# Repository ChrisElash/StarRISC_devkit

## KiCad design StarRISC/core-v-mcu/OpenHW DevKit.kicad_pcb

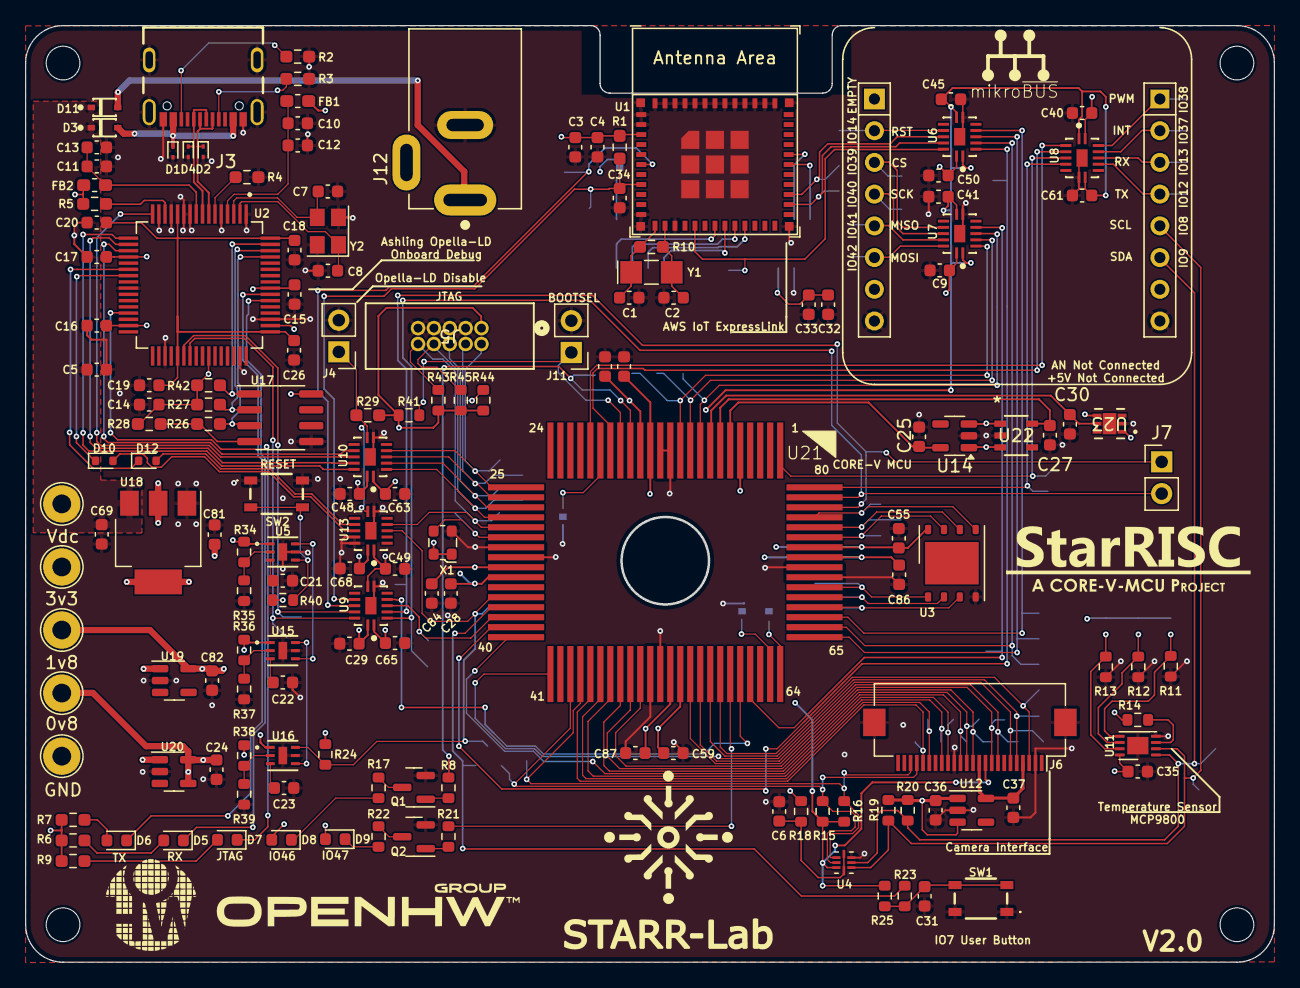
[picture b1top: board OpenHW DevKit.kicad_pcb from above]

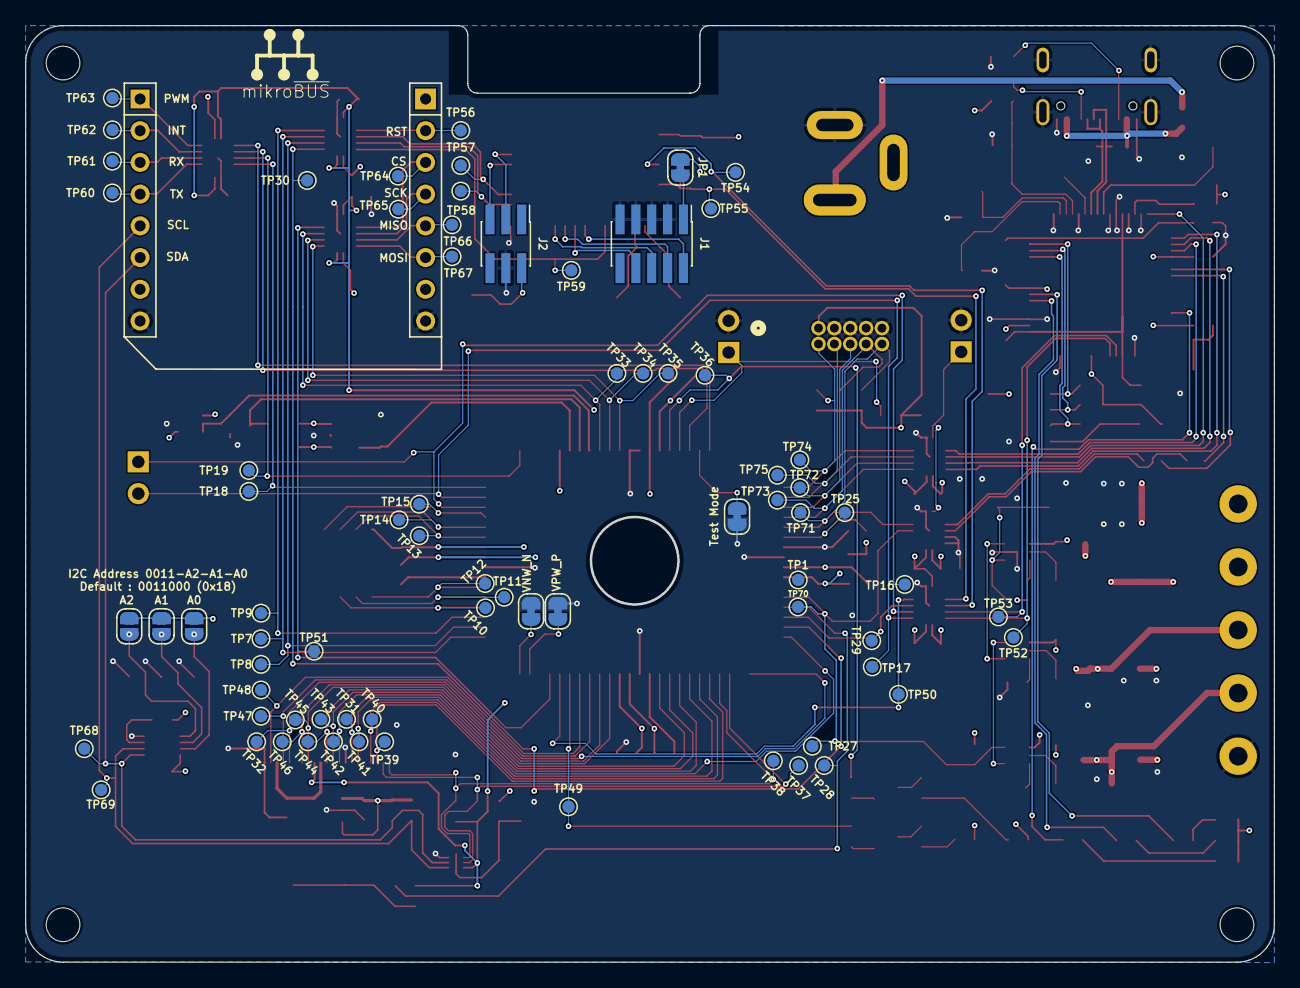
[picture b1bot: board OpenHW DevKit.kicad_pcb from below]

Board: 4 copper layers, 100.0 x 75.0 mm, 232 parts (73 on the bottom side), 139 nets.

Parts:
C1, C2, C7, C8: 12.5pF; C_0603_1608Metric
C3, C5, C30, C33, C69: 10uF; C_0603_1608Metric
C4, C6, C9, C12, C13, C14, C15, C16, C17, C18, C19, C20, C28, C29, C31, C34, C40, C41, C45, C48, C49, C50, C55, C57, C59, C61, C63, C65, C68, C84, C85, C86, C87: 100nF; C_0603_1608Metric
C10, C11: 4.7uF; C_0603_1608Metric
C21, C22, C23: 150pF; C_0603_1608Metric
C24, C25, C27, C36, C37, C82: 1uF; C_0603_1608Metric
C26: 3.3uF; C_0603_1608Metric
C32, C35: 100n; C_0603_1608Metric
C81: 22uF; C_0603_1608Metric
CON1: MIKROBUS_HOST_CONN
D1, D2, D4: ESD9B5.0ST5G; D_SOD-923
D3, D11: BAT760-7; Diodes-SOD323-03_2017-0-0
D5, D6, D7: LED_Small; LED_0603_1608Metric
D8, D9: LED; LED_0603_1608Metric
D10, D12: 1N914WT; D_SOD-523
FB1, FB2: Ferrite_Bead_Small; L_0603_1608Metric_Pad1.05x0.95mm_HandSolder
H1, H2, H3, H4: MountingHole; MountingHole_2.7mm_M2.5
J1: Conn_02x05_Odd_Even; PinHeader_2x05_P1.27mm_Vertical_SMD
J2: Conn_02x03_Odd_Even; PinHeader_2x03_P1.27mm_Vertical_SMD
J3: USB4105-GF-A; GCT_USB4105-GF-A
J4, J11: Conn_01x02_Male; PinHeader_1x02_P2.54mm_Vertical
J5: 3220-10-0100-00; CONN_3220-10-0100-00_CNC
J6: Conn_01x24; Hirose_FH12-24S-0.5SH_1x24-1MP_P0.50mm_Horizontal
J7: Conn_01x02_Pin; PinHeader_1x02_P2.54mm_Vertical
J12: PJ-002B; CUI_PJ-002B
JP1, JP2, JP6, JP9: SolderJumper_2_Bridged; SolderJumper-2_P1.3mm_Bridged_RoundedPad1.0x1.5mm
JP3, JP4, JP5: SolderJumper_2_Open; SolderJumper-2_P1.3mm_Open_RoundedPad1.0x1.5mm
Q1, Q2: MMBT3904; SOT-23
R1, R27, R28, R29, R42: 10k; R_0603_1608Metric_Pad0.98x0.95mm_HandSolder
R2, R3, R5: 5.1k; R_0603_1608Metric_Pad0.98x0.95mm_HandSolder
R4: 12k; R_0603_1608Metric_Pad0.98x0.95mm_HandSolder
R6, R7, R9, R26: 2.2k; R_0603_1608Metric_Pad0.98x0.95mm_HandSolder
R8, R21: 1k; R_0603_1608Metric
R10: 1M; R_0603_1608Metric_Pad0.98x0.95mm_HandSolder
R11, R12, R13, R14: 47k; R_0603_1608Metric
R15, R16, R19, R20, R25, R40: 4.7k; R_0603_1608Metric
R17, R22: 220; R_0603_1608Metric
R18: 200k; R_0603_1608Metric
R23: 100; R_0603_1608Metric
R24: 100k; R_0603_1608Metric
R34: 65k; R_0603_1608Metric
R35, R37, R39, R41, R43, R44, R45: 10k; R_0603_1608Metric
R36: 32.5k; R_0603_1608Metric
R38: 7.5k; R_0603_1608Metric
SW1, SW2: SW_Push; TS204225WT160SMTTR
TP1: TestPoint; TestPoint_Pad_D1.0mm
TP2: Vdc; TestPoint_Loop_D2.54mm_Drill1.5mm_Beaded
TP3: 3v3; TestPoint_Loop_D2.54mm_Drill1.5mm_Beaded
TP4: 1v8; TestPoint_Loop_D2.54mm_Drill1.5mm_Beaded
TP5: 0v8; TestPoint_Loop_D2.54mm_Drill1.5mm_Beaded
TP6: GND; TestPoint_Loop_D2.54mm_Drill1.5mm_Beaded
TP7, TP8, TP9, TP10, TP11, TP12, TP13, TP14, TP15, TP16, TP17, TP18, TP19, TP25, TP27, TP28, TP29, TP30, TP31, TP32, TP33, TP34, TP35, TP36, TP37, TP38, TP39, TP40, TP41, TP42, TP43, TP44, TP45, TP46, TP47, TP48, TP49, TP50, TP51, TP52, TP53, TP54, TP55, TP56, TP57, TP58, TP59, TP60, TP61, TP62, TP63, TP64, TP65, TP66, TP67, TP68, TP69, TP70, TP71, TP72, TP73, TP74, TP75: TestPoint_Small; TestPoint_Pad_D1.0mm
U1: ESP32-C3-MINI-1
U2: FT2232HL-REEL; QFP50P1200X1200X160-64N
U3: W25Q32JWZP; WSON-8-1EP_6x5mm_P1.27mm_EP3.4x4.3mm
U4: FXMA2102UMX
U5, U15, U16: MP6400DG-01-LF-Z; QFN6_MP6400_MNP
U6, U7, U8, U9, U10, U13: NTB0104BQ,115; NXP_Semiconductors-SOT762-1-08_2019-0-MFG
U11: MCP9808; DFN-8-1EP_3x2mm_P0.5mm_EP1.7x1.4mm
U12: AP2127K-2.8; SOT-23-5
U14: TLV71315PDBV; SOT-23-5
U17: 93C56; SOIC-8_3.9x4.9mm_P1.27mm
U18: AMS1117-3.3; SOT-223-3_TabPin2
U19: AP2127K-1.8; SOT-23-5
U20: AP2127K-ADJ; SOT-23-5
U21: 80CQFP
U22: ADP1711AUJZ-0.75R7; UJ_5_ADI
U23: NCV8135AMT040TBG; WDFN6-2x2_511BR_OSI
X1: ECS-2520MVLC-100-CN; Oscillator_SMD_ECS_2520MV-xxx-xx-4Pin_2.5x2.0mm
Y1: 32.768kHz; Crystal_SMD_MicroCrystal_CC7V-T1A-2Pin_3.2x1.5mm_HandSolder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
Y2: 12MHz; Crystal_SMD_Abracon_ABM8G-4Pin_3.2x2.5mm

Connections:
10MHZ_CLOCK_SOC: TP25.1, U21.30 (IO[5]), X1.3 (OUT)
+0V4: C30.1, U21.8 (PLL4), U23.5 (SNS), U23.6 (OUT)
+0V8: C24.1, C84.1, C85.1, C86.1, C87.1, R38.1, TP5.1, U20.4 (ADJ), U20.5 (VOUT), U21.5 (PLL1), U21.14 (VDDC), U21.33 (VDDC), U21.53 (VDDC), U21.73 (VDDC)
+0V75: C27.1, U21.7 (PLL3), U22.5 (OUT)
+1V5: C25.1, U14.5 (OUT), U21.6 (PLL2)
+1V8: C28.1, C41.1, C45.1, C49.1, C55.1, C57.1, C59.1, C61.1, C63.1, C65.1, C82.1, J5.1, J6.10, R15.2, R16.2, R24.1, R25.2, R29.2, R36.1, R41.2, R43.2, R44.2, R45.2, TP4.1, U3.8 (VCC), U4.8 (VCCB), U6.1 (VCC(A)), U6.8 (OE), U7.1 (VCC(A)), U7.8 (OE), U8.1 (VCC(A)), U8.8 (OE), U9.1 (VCC(A)), U9.8 (OE), U10.1 (VCC(A)), U13.1 (VCC(A)), U15.1 (VCC), U16.1 (VCC), U19.5 (VOUT), U21.15 (VDDIO), U21.34 (VDDIO), U21.54 (VDDIO), U21.74 (VDDIO), X1.1 (Tri-State), X1.4 (VDD)
+3V3: C3.1, C4.1, C9.1, C14.1, C15.1, C16.1, C17.1, C29.1, C32.1, C33.1, C35.1, C36.1, C40.1, C48.1, C50.1, C68.1, C81.1, CON1.P7 (3V3), D8.2 (A), D9.2 (A), FB1.1, FB2.1, J2.2, JP1.1 (A), JP3.2 (B), JP4.2 (B), JP5.2 (B), R1.1, R5.1, R6.2, R7.2, R9.2, R14.1, R18.2, R19.2, R20.2, R27.2, R28.2, R34.1, R40.2, R42.2, TP3.1, U1.3 (3V3), U2.20 (VCCIO-1), U2.31 (VCCIO-2), U2.42 (VCCIO-3), U2.50 (VREGIN), U2.56 (VCCIO-4), U5.1 (VCC), U6.14 (VCC(B)), U7.14 (VCC(B)), U8.14 (VCC(B)), U9.14 (VCC(B)), U10.14 (VCC(B)), U11.8 (VDD), U12.1 (VIN), U12.3 (EN), U13.14 (VCC(B)), U14.1 (IN), U14.3 (EN), U17.8 (VCC), U18.2 (VO), U19.1 (VIN), U20.1 (VIN), U22.1 (IN), U22.3 (EN), U23.1 (IN), U23.4 (EN)
+VDC: C5.1, C69.1, D3.1 (CATHODE), D11.1 (CATHODE), TP2.1, U18.3 (VI)
/CLICK_CS: CON1.P3 (CS), TP64.1, U7.10 (B4)
/CLICK_INT: CON1.P15 (INT), TP62.1, U8.12 (B2)
/CLICK_MISO: CON1.P5 (MISO), TP66.1, U7.12 (B2)
/CLICK_MOSI: CON1.P6 (MOSI), TP67.1, U7.13 (B1)
/CLICK_PWM: CON1.P16 (PWM), TP63.1, U8.13 (B1)
/CLICK_RST: CON1.P2 (RST), TP56.1, U6.10 (B4)
/CLICK_RX: CON1.P14 (RX), TP61.1, U8.11 (B3)
/CLICK_SCK: CON1.P4 (SCK), TP65.1, U7.11 (B3)
/CLICK_TX: CON1.P13 (TX), TP60.1, U8.10 (B4)
/EL_EVENT: TP59.1, U1.16 (GPIO10), U6.13 (B1)
/EL_RXD: TP57.1, U1.27 (GPIO19/USB_D+), U6.11 (B3)
/EL_TXD: TP58.1, U1.26 (GPIO18/USB_D-), U6.12 (B2)
/EL_WAKE: TP54.1, U1.6 (GPIO3/ADC1_CH3), U9.11 (B3)
/Power Supply/~RESET_IN: R40.1, SW2.2, U5.4 (*MR)
/VNW_N: JP6.2 (B), U21.64 (NMOS)
/VPW_P: JP2.2 (B), U21.63 (PMOS)
/camera/2v8: C37.1, J6.4, J6.11, U12.5 (VOUT)
/jtag and uart/VBUS: D1.1 (A1), D3.2 (ANODE), J3.A4_B9 (VBUS), J3.B4_A9 (VBUS__1)
/jtag and uart/d+: D4.1 (A1), J3.A6 (DP1), J3.B6 (DP2), U2.8 (DP)
/jtag and uart/d-: D2.1 (A1), J3.A7 (DN1), J3.B7 (DN2), U2.7 (DM)
/mikrobus and sensors/temperature_alert: R14.2, U11.3 (Alert)
/~EL_RESET: C34.1, R1.2, TP55.1, U1.8 (EN/CHIP_PU), U9.10 (B4)
BOOTSEL: J11.1, R41.1, U21.17 (IO[44])
CAMERA_D0: J6.14, TP42.1, U21.48 (IO[29])
CAMERA_D1: J6.3, TP48.1, U21.58 (IO[30])
CAMERA_D2: J6.9, TP45.1, U21.55 (IO[31])
CAMERA_D3: J6.5, TP47.1, U21.57 (IO[32])
CAMERA_D4: J6.12, TP44.1, U21.50 (IO[33])
CAMERA_D5: J6.20, TP39.1, U21.45 (IO[34])
CAMERA_D6: J6.19, TP40.1, U21.46 (IO[35])
CAMERA_D7: J6.13, TP43.1, U21.49 (IO[36])
CAMERA_HSYNC: J6.16, TP31.1, U21.40 (IO[22])
CAMERA_MCLK: J6.8, TP46.1, U21.56 (IO[26])
CAMERA_PCLK: J6.17, TP41.1, U21.47 (IO[25])
CAMERA_VSYNC: J6.6, TP32.1, U21.41 (IO[21])
CLICK_IRQ_SOC: U8.3 (A2), U21.18 (IO[37])
CLICK_PWM_SOC: U8.2 (A1), U21.20 (IO[42])
CLICK_RESET_SOC: TP9.1, U6.5 (A4), U21.67 (IO[18])
CONSOLE_RX: TP52.1, U2.39 (BDBUS1), U9.13 (B1)
CONSOLE_TX: TP53.1, U2.38 (BDBUS0), U9.12 (B2)
CS0_SOC: TP51.1, U7.5 (A4), U21.61 (IO[38])
EE_CS: R42.1, U2.63 (EECS), U17.1 (CS)
EE_DATA: R26.1, U2.61 (EEDATA), U17.3 (DI)
EE_SCLK: R27.1, U2.62 (EECLK), U17.2 (SCLK)
EL_EVENT_SOC: TP30.1, U6.2 (A1), U21.39 (IO[24])
EL_WAKE_SOC: TP29.1, U9.4 (A3), U21.38 (IO[23])
FPGA_LED0: R21.2, TP49.1, U21.59 (IO[28])
GND: C1.2, C2.2, C3.2, C4.2, C5.2, C6.2, C7.2, C8.2, C9.2, C10.2, C11.2, C12.2, C13.2, C14.2, C15.2, C16.2, C17.2, C18.2, C19.2, C20.2, C21.2, C22.2, C23.2, C24.2, C25.2, C26.2, C27.2, C28.2, C29.2, C30.2, C31.2, C32.2, C33.2, C34.2, C35.2, C36.2, C37.2, C40.2, C41.2, C45.2, C48.2, C49.2, C50.2, C55.2, C57.2, C59.2, C61.2, C63.2, C65.2, C68.2, C69.2, C81.2, C82.2, C84.2, C85.2, C86.2, C87.2, CON1.P8 (GND1), CON1.P9 (GND2), D1.2 (A2), D2.2 (A2), D4.2 (A2), J1.3, J1.5, J1.7, J1.9, J2.4, J3.A1_B12 (GND), J3.B1_A12 (GND__1), J3.S1 (SHELL_GND), J3.S2 (SHELL_GND__1), J3.S3 (SHELL_GND__2), J3.S4 (SHELL_GND__3), J4.2, J5.3, J5.5, J5.7, J5.9, J6.2, J6.15, J6.MP (MountPin), J11.2, J12.2, JP2.1 (A), JP6.1 (A), JP9.2 (B), Q1.2 (E), Q2.2 (E), R2.2, R3.2, R4.2, R11.2, R12.2, R13.2, R35.2, R37.2, R39.2, SW1.1, SW2.1, TP6.1, U1.1 (GND), U1.2 (GND), U1.11 (GND), U1.14 (GND), U1.36 (GND), U2.1 (GND), U2.5 (GND), U2.10 (AGND), U2.11 (GND), U2.13 (TEST), U2.15 (GND), U2.25 (GND), U2.35 (GND), U2.47 (GND), U2.51 (GND), U3.4 (GND), U4.4 (GND), U5.5 (GND), U5.7 (EPAD), U6.7 (GND), U6.15 (GND), U7.7 (GND), U7.15 (GND), U8.7 (GND), U8.15 (GND), U9.7 (GND), U9.15 (GND), U10.7 (GND), U10.15 (GND), U11.4 (GND), U11.9 (EP/GND), U12.2 (GND), U13.7 (GND), U13.12 (B2), U13.13 (B1), U13.15 (GND), U14.2 (GND), U15.5 (GND), U15.7 (EPAD), U16.5 (GND), U16.7 (EPAD), U17.5 (GND), U18.1 (GND), U19.2 (GND), U20.2 (GND), U21.12 (VSSIO), U21.13 (VSSC), U21.31 (VSSIO), U21.32 (VSSC), U21.51 (VSSIO), U21.52 (VSSC), U21.71 (VSSIO), U21.72 (VSSC), U22.2 (GND), U23.2 (GND), X1.2 (GND), Y2.2, Y2.4
MISO0_SOC: TP34.1, U7.3 (A2), U21.10 (IO[41])
MOSI0_SOC: TP35.1, U7.2 (A1), U21.11 (IO[39])
unnamed: C31.1, R23.1, R25.1, SW1.2
unnamed: D5.2 (A), R6.1
unnamed: D5.1 (K), U2.54 (BCBUS3)
unnamed: D6.2 (A), R7.1
unnamed: D6.1 (K), U2.55 (BCBUS4)
unnamed: D7.2 (A), R9.1
unnamed: D7.1 (K), U2.29 (ACBUS3)
unnamed: D8.1 (K), R17.2
unnamed: D9.1 (K), R22.2
unnamed: D10.2 (A), U13.11 (B3)
unnamed: D10.1 (K), U2.23 (ADBUS6)
unnamed: D11.2 (ANODE), J12.1
unnamed: D12.2 (A), U13.10 (B4)
unnamed: D12.1 (K), U2.22 (ADBUS5)
unnamed: J1.1, JP1.2 (B)
unnamed: J1.2, U1.18 (GPIO4/ADC1_CH4)
unnamed: J1.4, U1.20 (GPIO6)
unnamed: J1.6, U1.21 (GPIO7)
unnamed: J1.8, U1.19 (GPIO5/ADC2_CH0)
unnamed: J2.3, U1.31 (GPIO21/U0TXD)
unnamed: J2.5, U1.30 (GPIO20/U0RXD)
unnamed: J3.A5 (CC1), R3.1
unnamed: J3.B5 (CC2), R2.1
unnamed: J4.1, R29.1, U10.8 (OE), U13.8 (OE)
unnamed: JP3.1 (A), R11.1, U11.5 (A2)
unnamed: JP4.1 (A), R12.1, U11.6 (A1)
unnamed: JP5.1 (A), R13.1, U11.7 (A0)
unnamed: Q1.1 (B), R8.1
unnamed: Q1.3 (C), R17.1
unnamed: Q2.1 (B), R21.1
unnamed: Q2.3 (C), R22.1
unnamed: C1.1, R10.1, U1.12 (GPIO0/ADC1_CH0/XTAL_32K_P), Y1.1
unnamed: C2.1, R10.2, U1.13 (GPIO1/ADC1_CH1/XTAL_32K_N), Y1.2
unnamed: R4.1, U2.6 (REF)
unnamed: C18.1, C19.1, C20.1, C26.1, U2.12 (VCORE-1), U2.37 (VCORE-2), U2.49 (VREGOUT), U2.64 (VCORE-3)
unnamed: C10.1, C12.1, FB1.2, U2.4 (VPHY)
unnamed: C11.1, C13.1, FB2.2, U2.9 (VPLL)
unnamed: R5.2, U2.14 (~RESET)
unnamed: C6.1, R18.1, U4.1 (VCCA), U4.5 (OE)
unnamed: C21.1, U5.3 (CDELAY)
unnamed: R34.2, R35.1, U5.2 (SENSE)
unnamed: U2.17 (ADBUS1), U10.13 (B1)
unnamed: U2.18 (ADBUS2), U10.12 (B2)
unnamed: U2.16 (ADBUS0), U10.11 (B3)
unnamed: U2.19 (ADBUS3), U10.10 (B4)
unnamed: U5.6 (*RESET), U15.4 (*MR)
unnamed: U15.6 (*RESET), U16.4 (*MR)
unnamed: C22.1, U15.3 (CDELAY)
unnamed: R36.2, R37.1, U15.2 (SENSE)
unnamed: C23.1, U16.3 (CDELAY)
unnamed: R38.2, R39.1, U16.2 (SENSE)
unnamed: R26.2, R28.1, U17.4 (DO)
PGM_FLASH_CLK: TP14.1, U3.6 (CLK), U21.76 (IO[16])
PGM_FLASH_CS: TP12.1, U3.1 (~CS), U21.70 (IO[13])
PGM_FLASH_DATA0: TP15.1, U3.5 (DI(IO0)), U21.77 (IO[14])
PGM_FLASH_DATA1: TP11.1, U3.2 (DO(IO1)), U21.69 (IO[15])
PGM_FLASH_DATA2: TP10.1, U3.3 (IO2), U21.68 (IO[19])
PGM_FLASH_DATA3: TP13.1, U3.7 (IO3), U21.75 (IO[20])
RX1_MUX0_SOC: TP8.1, U6.3 (A2), U21.66 (IO[12])
RX1_MUX1_SOC: TP19.1, U8.4 (A3), U21.1 (IO[10])
SCL: CON1.P12 (SCL), R19.1, TP69.1, U4.2 (A0), U11.2 (SCL)
SCL0_SOC: J6.21, R15.1, TP37.1, U4.7 (B0), U21.43 (IO[46])
SCLK0_SOC: TP33.1, U7.4 (A3), U21.9 (IO[40])
SDA: CON1.P11 (SDA), R20.1, TP68.1, U4.3 (A1), U11.1 (SDA)
SDA0_SOC: J6.22, R16.1, TP38.1, U4.6 (B1), U21.44 (IO[47])
TCK: J5.4, TP75.1, U10.4 (A3), U21.26 (IO[0])
TDI: J5.8, R45.1, TP73.1, U10.2 (A1), U21.28 (IO[1])
TDO: J5.6, TP72.1, U10.3 (A2), U21.27 (IO[2])
TEST_MODE: JP9.1 (A), U21.19 (IO[45])
TMS: J5.2, R44.1, TP74.1, U10.5 (A4), U21.25 (IO[3])
TRST: J5.10, R43.1, TP71.1, U13.5 (A4), U21.29 (IO[4])
TX0_RXD: J7.1, TP16.1, U9.3 (A2), U21.78 (IO[7])
TX0_TXD: J7.2, TP17.1, U9.2 (A1), U21.79 (IO[8])
TX1_MUX0_SOC: TP7.1, U6.4 (A3), U21.65 (IO[11])
TX1_MUX1_SOC: TP18.1, U8.5 (A4), U21.80 (IO[9])
USER_BUTTON: R23.2, TP28.1, U21.37 (IO[17])
USER_LED_SOC: R8.2, TP36.1, U21.16 (IO[27])
osci: C8.1, U2.2 (OSCI), Y2.1
osco: C7.1, U2.3 (OSCO), Y2.3
~EL_RESET_SOC: TP50.1, U9.5 (A4), U21.60 (IO[43])
~RESET_SOC: R24.2, TP27.1, TP70.1, U13.4 (A3), U16.6 (*RESET), U21.36 (IO[6])

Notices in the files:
parts and their libraries:
Copyright 2021 Accelerated Designs. All rights reserved.
